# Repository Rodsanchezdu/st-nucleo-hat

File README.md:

# st-nucleo-hat
Hat for the NUCLEO-F767ZI

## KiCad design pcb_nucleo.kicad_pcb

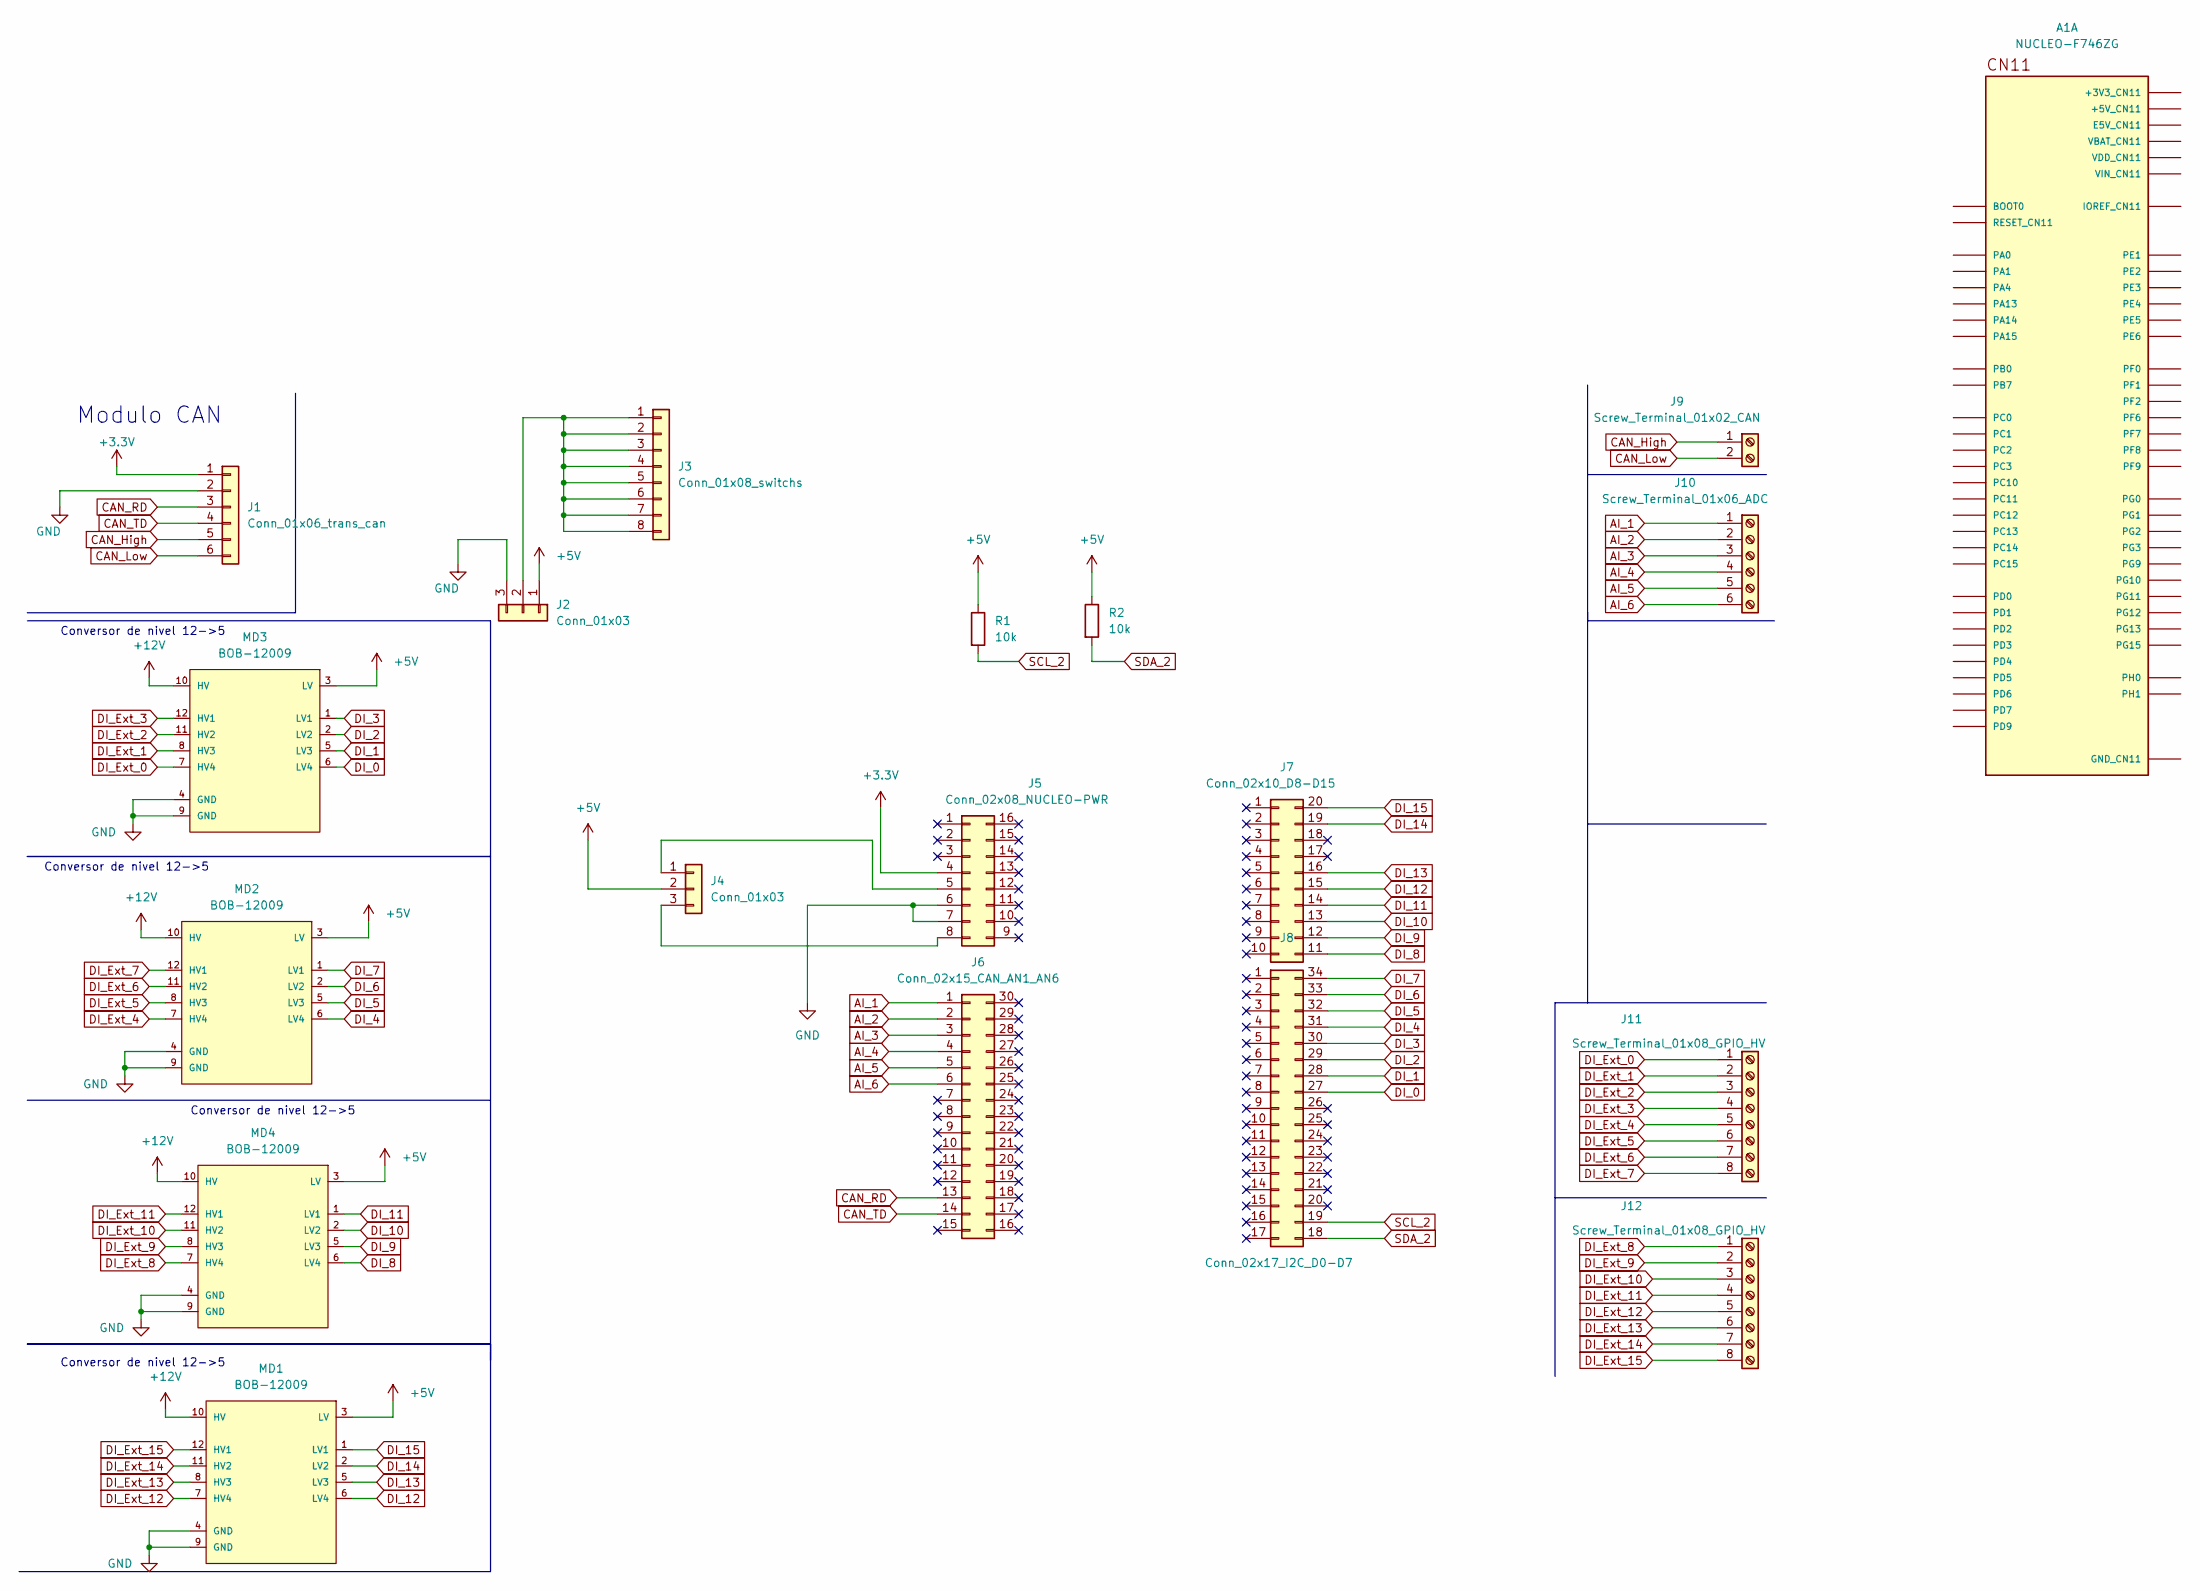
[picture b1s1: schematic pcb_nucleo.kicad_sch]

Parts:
A1: NUCLEO-F746ZG; MODULE_NUCLEO-F746ZG; PARTREV 7
J1: Conn_01x06_trans_can; PinSocket_1x06_P2.54mm_Vertical
J2, J4: Conn_01x03; PinHeader_1x03_P2.54mm_Vertical
J3: Conn_01x08_switchs; PinHeader_1x08_P2.54mm_Vertical
J5: Conn_02x08_NUCLEO-PWR; PinSocket_2x08_P2.54mm_Vertical
J6: Conn_02x15_CAN_AN1_AN6; PinSocket_2x15_P2.54mm_Vertical
J7: Conn_02x10_D8-D15; PinSocket_2x10_P2.54mm_Vertical
J8: Conn_02x17_I2C_D0-D7; PinSocket_2x17_P2.54mm_Vertical
J9: Screw_Terminal_01x02_CAN; TerminalBlock_Phoenix_MKDS-1,5-2-5.08_1x02_P5.08mm_Horizont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
J10: Screw_Terminal_01x06_ADC; TerminalBlock_Phoenix_MKDS-1,5-6-5.08_1x06_P5.08mm_Horizont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
J11, J12: Screw_Terminal_01x08_GPIO_HV; TerminalBlock_Phoenix_MKDS-1,5-8-5.08_1x08_P5.08mm_Horizont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
MD1, MD2, MD3, MD4: BOB-12009; SparkFun-BOB-12009-MFG; mouser part number 474-BOB-12009; digikey description LOGIC LEVEL CONVERTER - BI-DIREC
R1, R2: 10k; R_Axial_DIN0204_L3.6mm_D1.6mm_P5.08mm_Horizontal

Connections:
+3V3: J1.1, J5.4
+5V: J2.1, J4.2, MD1.3 (LV), MD2.3 (LV), MD3.3 (LV), MD4.3 (LV), R1.1, R2.1
+12V: MD1.10 (HV), MD2.10 (HV), MD3.10 (HV), MD4.10 (HV)
AI_1: J6.1, J10.1
AI_2: J6.2, J10.2
AI_3: J6.3, J10.3
AI_4: J6.4, J10.4
AI_5: J6.5, J10.5
AI_6: J6.6, J10.6
CAN_High: J1.5, J9.1
CAN_Low: J1.6, J9.2
CAN_RD: J1.3, J6.13
CAN_TD: J1.4, J6.14
DI_0: J8.27, MD3.6 (LV4)
DI_1: J8.28, MD3.5 (LV3)
DI_2: J8.29, MD3.2 (LV2)
DI_3: J8.30, MD3.1 (LV1)
DI_4: J8.31, MD2.6 (LV4)
DI_5: J8.32, MD2.5 (LV3)
DI_6: J8.33, MD2.2 (LV2)
DI_7: J8.34, MD2.1 (LV1)
DI_8: J7.11, MD4.6 (LV4)
DI_9: J7.12, MD4.5 (LV3)
DI_10: J7.13, MD4.2 (LV2)
DI_11: J7.14, MD4.1 (LV1)
DI_12: J7.15, MD1.6 (LV4)
DI_13: J7.16, MD1.5 (LV3)
DI_14: J7.19, MD1.2 (LV2)
DI_15: J7.20, MD1.1 (LV1)
DI_Ext_0: J11.1, MD3.7 (HV4)
DI_Ext_1: J11.2, MD3.8 (HV3)
DI_Ext_2: J11.3, MD3.11 (HV2)
DI_Ext_3: J11.4, MD3.12 (HV1)
DI_Ext_4: J11.5, MD2.7 (HV4)
DI_Ext_5: J11.6, MD2.8 (HV3)
DI_Ext_6: J11.7, MD2.11 (HV2)
DI_Ext_7: J11.8, MD2.12 (HV1)
DI_Ext_8: J12.1, MD4.7 (HV4)
DI_Ext_9: J12.2, MD4.8 (HV3)
DI_Ext_10: J12.3, MD4.11 (HV2)
DI_Ext_11: J12.4, MD4.12 (HV1)
DI_Ext_12: J12.5, MD1.7 (HV4)
DI_Ext_13: J12.6, MD1.8 (HV3)
DI_Ext_14: J12.7, MD1.11 (HV2)
DI_Ext_15: J12.8, MD1.12 (HV1)
GND: J1.2, J2.3, J5.6, J5.7, MD1.4 (GND), MD1.9 (GND), MD2.4 (GND), MD2.9 (GND), MD3.4 (GND), MD3.9 (GND), MD4.4 (GND), MD4.9 (GND)
unnamed: A1.CN11_8 (GND_CN11), A1.CN11_19 (GND_CN11), A1.CN11_20 (GND_CN11), A1.CN11_22 (GND_CN11), A1.CN11_49 (GND_CN11), A1.CN11_60 (GND_CN11), A1.CN11_71 (GND_CN11), A1.CN11_72 (GND_CN11)
unnamed: J2.2, J3.1, J3.2, J3.3, J3.4, J3.5, J3.6, J3.7, J3.8
unnamed: J4.1, J5.5
unnamed: J4.3, J5.8
SCL_2: J8.19, R1.2
SDA_2: J8.18, R2.2

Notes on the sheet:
Conversor de nivel 12->5
Modulo CAN

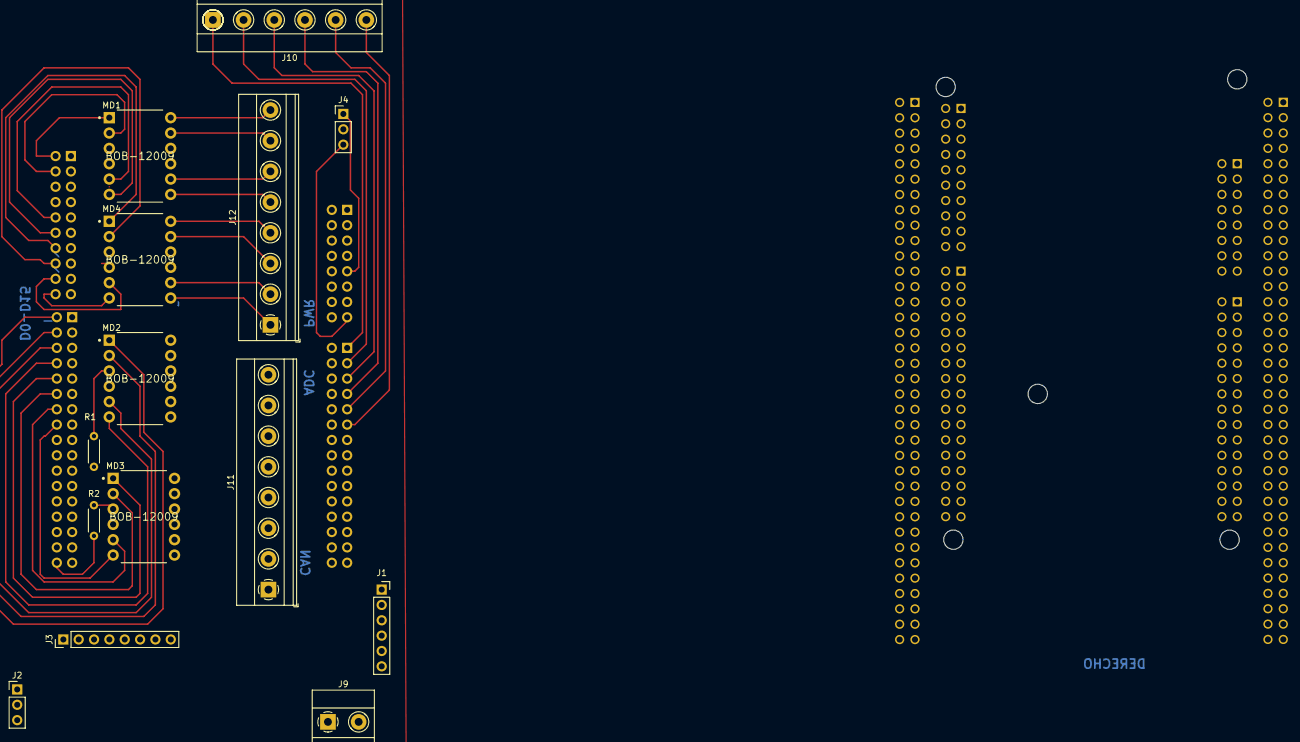
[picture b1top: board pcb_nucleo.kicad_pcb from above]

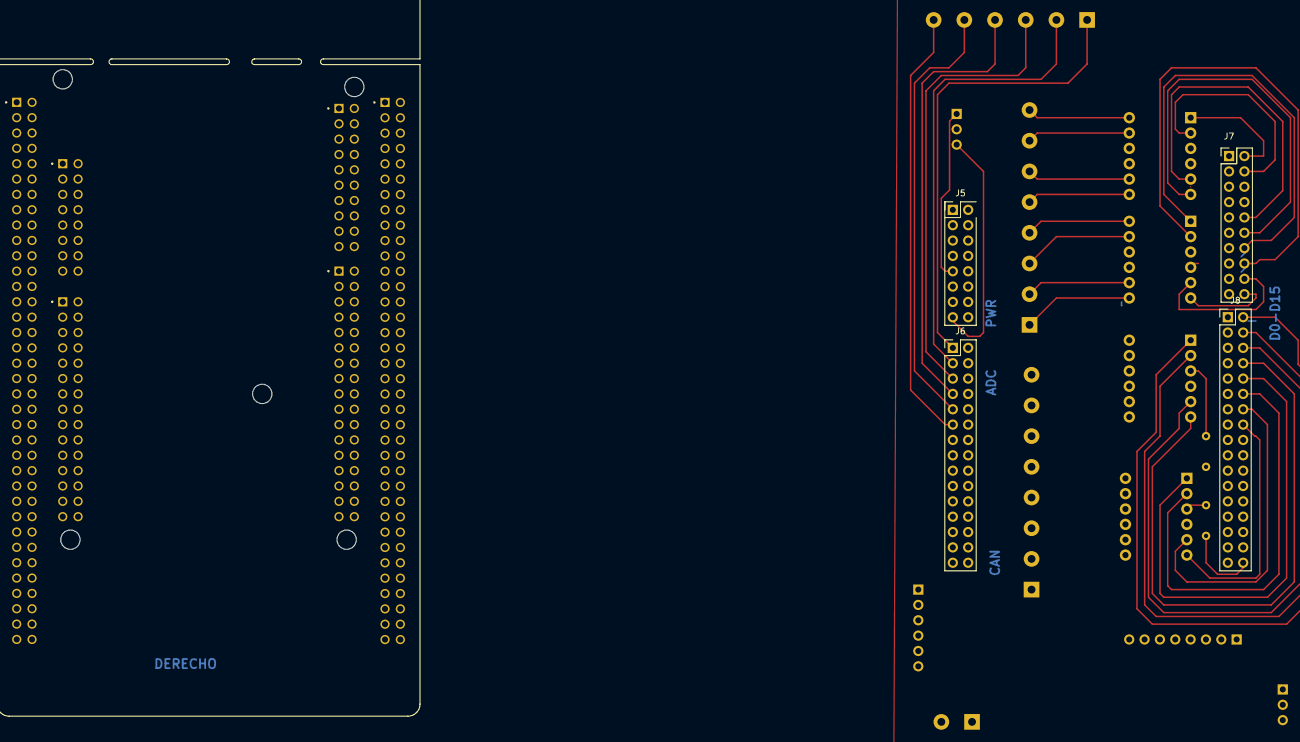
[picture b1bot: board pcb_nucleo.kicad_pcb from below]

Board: 2 copper layers, 19 parts (5 on the bottom side), 52 nets.

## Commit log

2022-08-23 init
